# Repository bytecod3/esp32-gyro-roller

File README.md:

Implement a rolling platform using MPU6050 on a SSD1306 OLED screen using ESP32 IDF

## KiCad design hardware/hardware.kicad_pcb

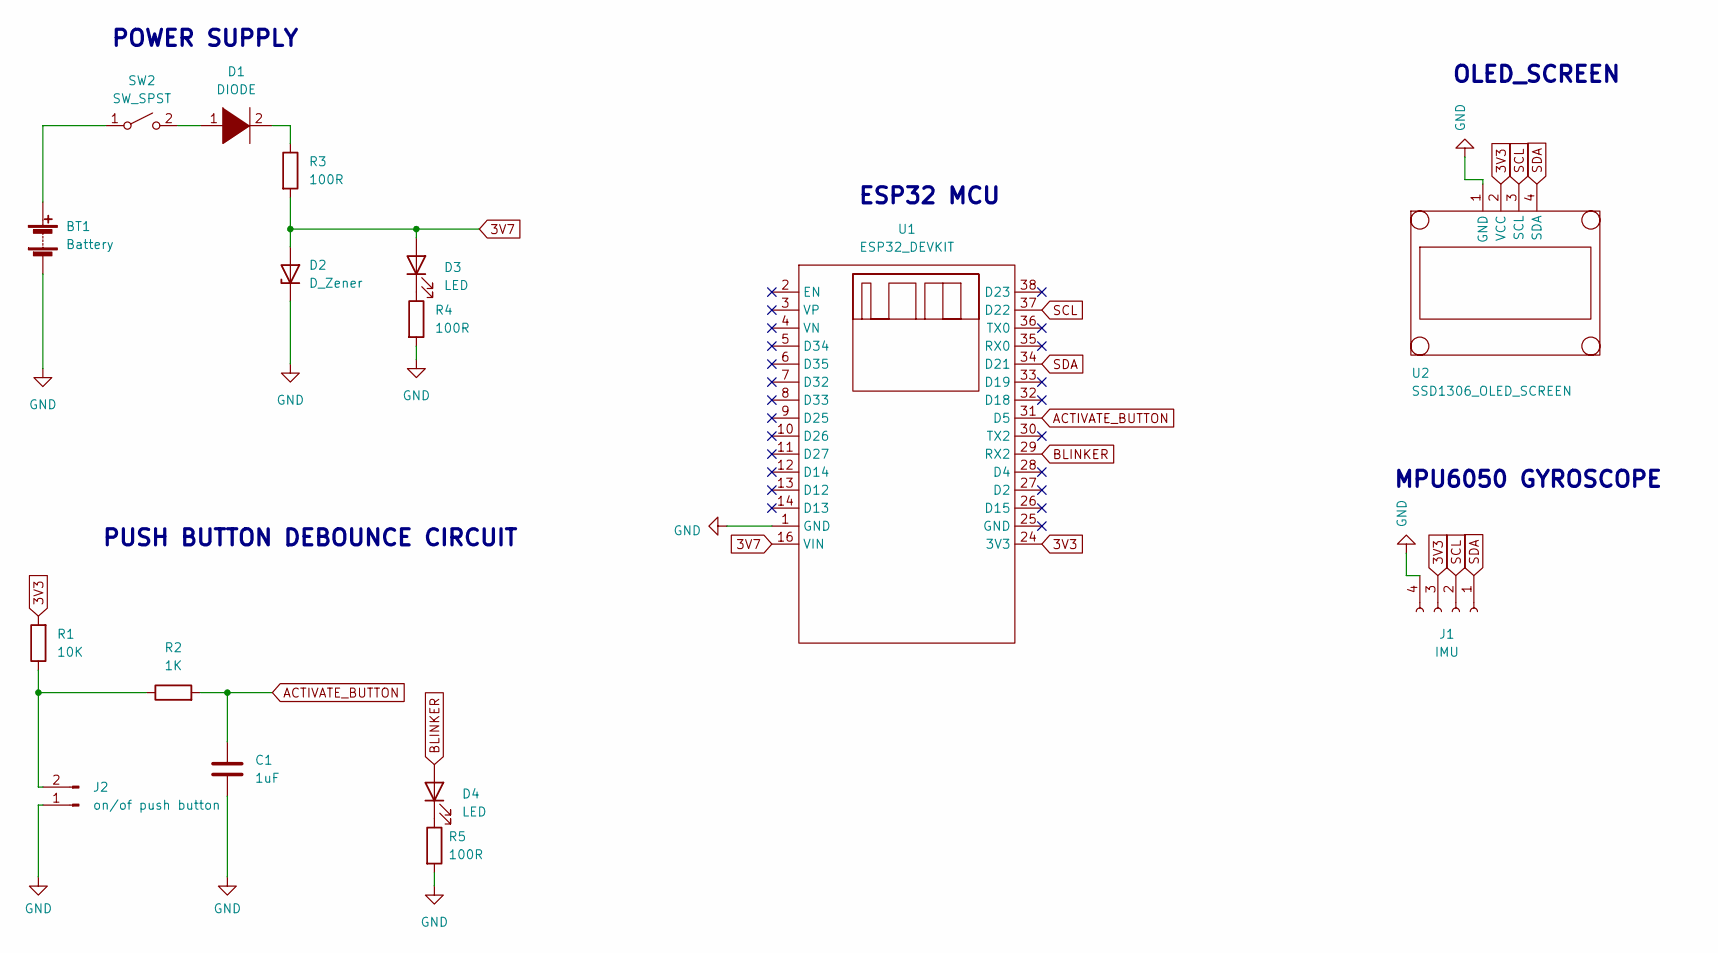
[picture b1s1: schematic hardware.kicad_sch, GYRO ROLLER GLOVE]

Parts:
BT1: Battery; PinHeader_1x02_P2.54mm_Vertical
C1: 1uF; CP_Radial_D4.0mm_P2.00mm
D1: DIODE; D_A-405_P7.62mm_Horizontal
D2: D_Zener; D_A-405_P7.62mm_Horizontal
D3, D4: LED; LED_D3.0mm
J1: IMU; PinHeader_1x04_P2.54mm_Vertical
J2: on/of push button; PinHeader_1x02_P2.54mm_Vertical
R1: 10K; R_Axial_DIN0204_L3.6mm_D1.6mm_P7.62mm_Horizontal
R2: 1K; R_Axial_DIN0204_L3.6mm_D1.6mm_P7.62mm_Horizontal
R3, R4, R5: 100R; R_Axial_DIN0204_L3.6mm_D1.6mm_P7.62mm_Horizontal
SW2: SW_SPST; PinHeader_1x03_P2.54mm_Vertical
U1: ESP32_DEVKIT
U2: SSD1306_OLED_SCREEN

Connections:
3V3: J1.3, R1.2, U1.24 (3V3), U2.2 (VCC)
3V7: D2.2 (A), D3.2 (A), R3.2, U1.16 (VIN)
ACTIVATE_BUTTON: C1.1, R2.2, U1.31 (D5)
BLINKER: D4.2 (A), U1.29 (RX2)
GND: BT1.2 (-), C1.2, D2.1 (K), J1.4, J2.1, R4.2, R5.2, U1.1 (GND), U2.1 (GND)
unnamed: BT1.1 (+), SW2.1 (A)
unnamed: D1.1 (K), SW2.2 (B)
unnamed: D1.2 (A), R3.1
unnamed: D3.1 (K), R4.1
unnamed: D4.1 (K), R5.1
unnamed: J2.2, R1.1, R2.1
SCL: J1.2, U1.37 (D22), U2.3 (SCL)
SDA: J1.1, U1.34 (D21), U2.4 (SDA)

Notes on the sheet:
OLED_SCREEN
POWER SUPPLY
MPU6050 GYROSCOPE
PUSH BUTTON DEBOUNCE CIRCUIT
ESP32 MCU

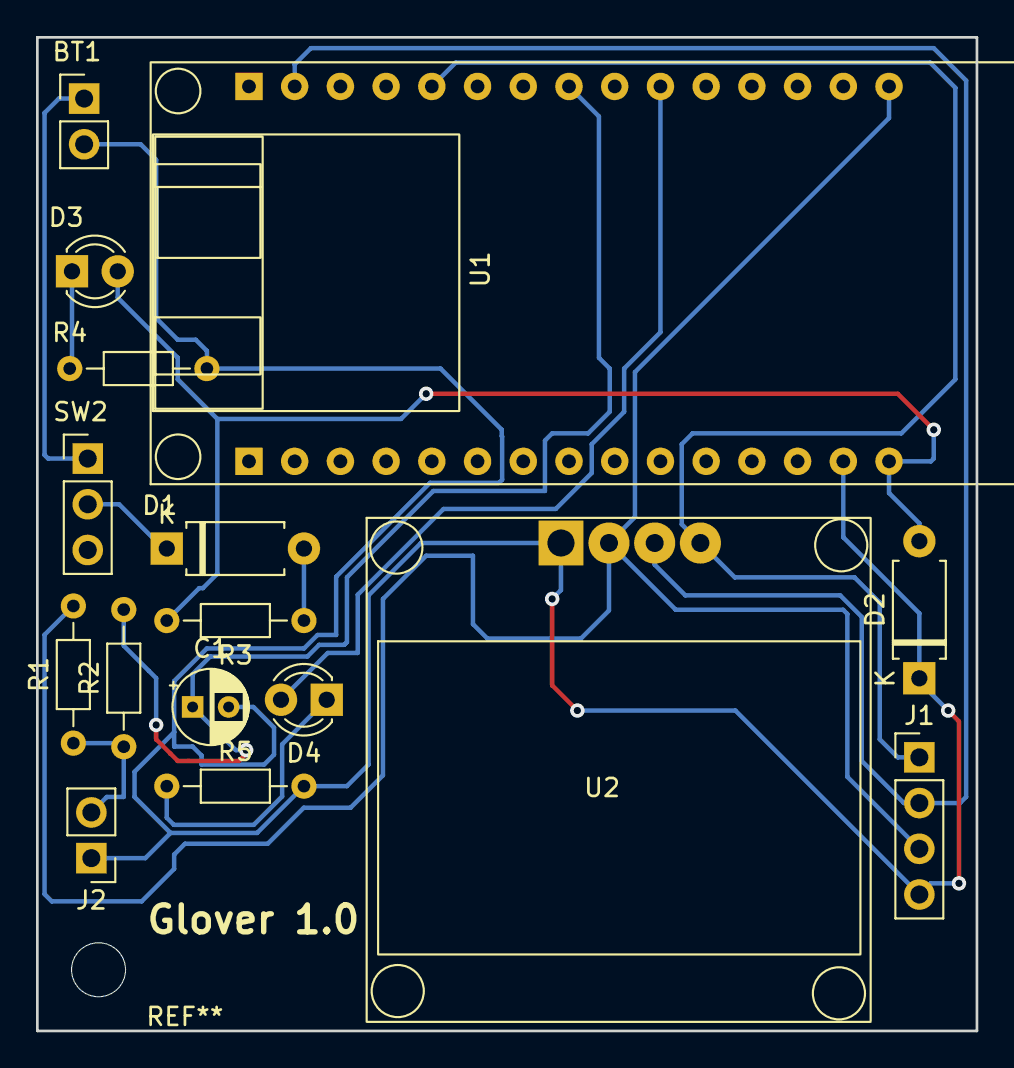
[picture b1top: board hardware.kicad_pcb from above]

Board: 2 copper layers, 52.2 x 55.2 mm, 16 parts (0 on the bottom side), 13 nets.

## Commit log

2023-01-27 added update circle function
2023-01-28 added target draw function
2023-01-28 added mpu6050 setup
2023-01-28 added wheel update function with x-offset values
2023-01-31 implemented polar coordinates
2023-01-31 added tiller update function using fillRect()
2023-02-01 finished marker updating on the screen using polar coordinates
2023-02-02 added HTTP asynchronous server for data transmission
2023-02-25 removed screen code
